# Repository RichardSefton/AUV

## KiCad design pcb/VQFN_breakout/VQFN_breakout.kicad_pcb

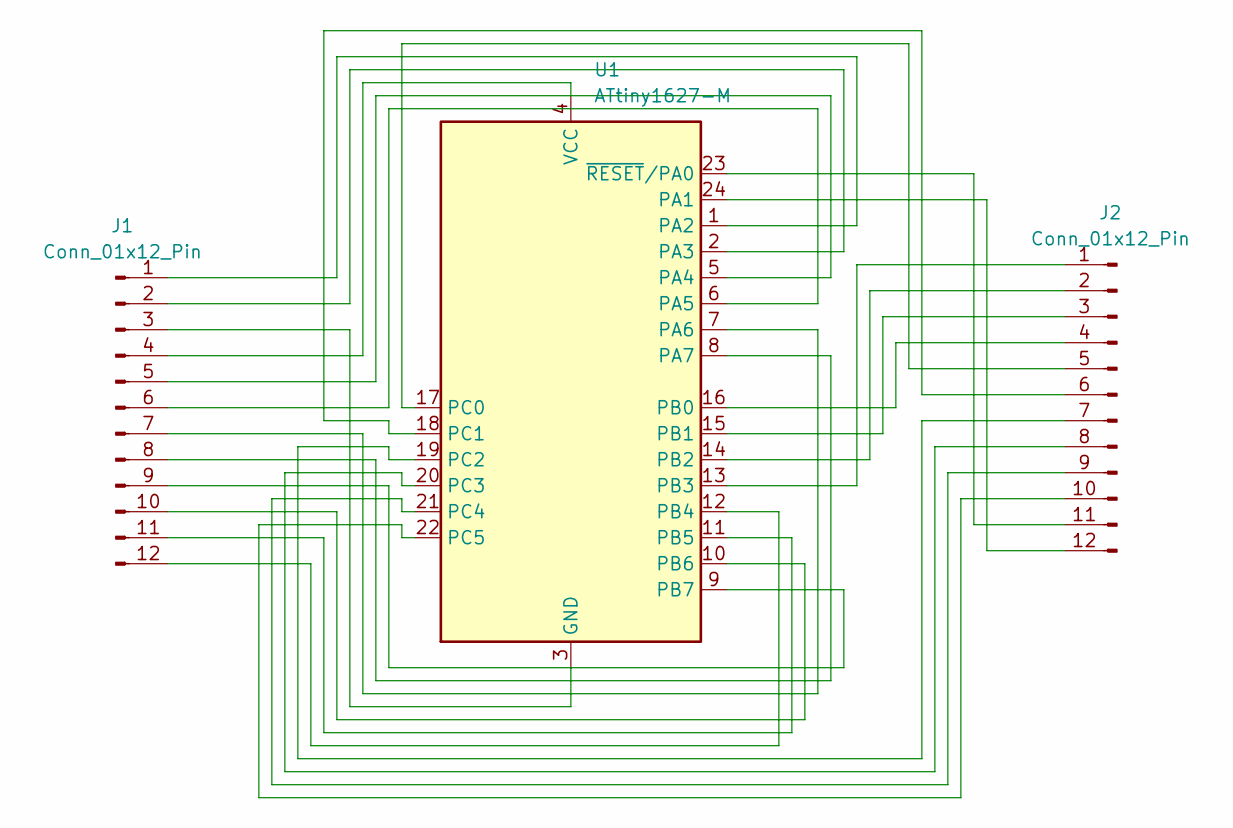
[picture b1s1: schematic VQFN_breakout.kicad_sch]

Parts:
J1, J2: Conn_01x12_Pin; PinSocket_1x12_P2.54mm_Vertical
U1: ATtiny1627-M; QFN-24-1EP_4x4mm_P0.5mm_EP2.6x2.6mm

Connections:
unnamed: J1.1, U1.1 (PA2)
unnamed: J1.2, U1.2 (PA3)
unnamed: J1.3, U1.3 (GND), U1.25 (GND)
unnamed: J1.4, U1.4 (VCC)
unnamed: J1.5, U1.5 (PA4)
unnamed: J1.6, U1.6 (PA5)
unnamed: J1.7, U1.7 (PA6)
unnamed: J1.8, U1.8 (PA7)
unnamed: J1.9, U1.9 (PB7)
unnamed: J1.10, U1.10 (PB6)
unnamed: J1.11, U1.11 (PB5)
unnamed: J1.12, U1.12 (PB4)
unnamed: J2.1, U1.13 (PB3)
unnamed: J2.2, U1.14 (PB2)
unnamed: J2.3, U1.15 (PB1)
unnamed: J2.4, U1.16 (PB0)
unnamed: J2.5, U1.17 (PC0)
unnamed: J2.6, U1.18 (PC1)
unnamed: J2.7, U1.19 (PC2)
unnamed: J2.8, U1.20 (PC3)
unnamed: J2.9, U1.21 (PC4)
unnamed: J2.10, U1.22 (PC5)
unnamed: J2.11, U1.23 (~RESET/PA0)
unnamed: J2.12, U1.24 (PA1)

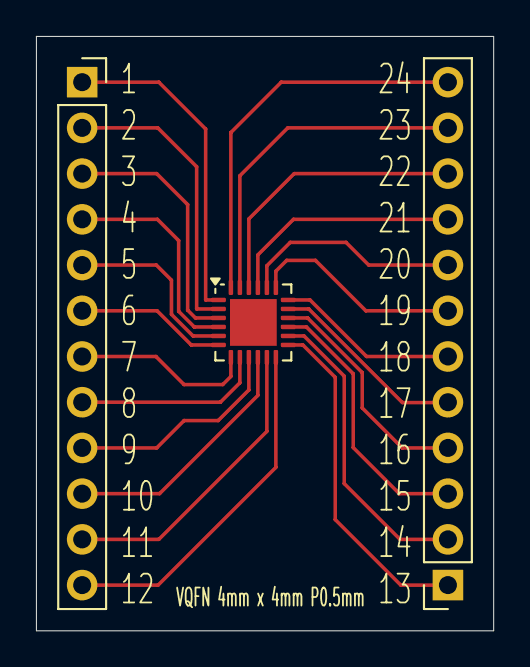
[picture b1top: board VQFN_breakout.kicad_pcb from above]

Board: 2 copper layers, 25.4 x 33.0 mm, 3 parts (0 on the bottom side), 24 nets.

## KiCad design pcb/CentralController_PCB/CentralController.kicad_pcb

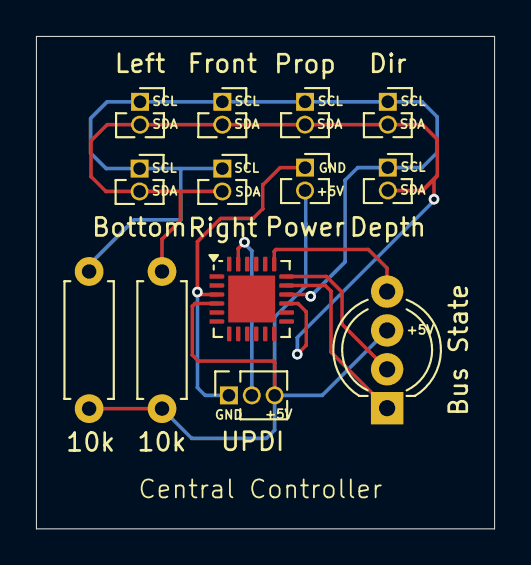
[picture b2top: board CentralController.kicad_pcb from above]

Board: 2 copper layers, 25.5 x 27.4 mm, 13 parts (0 on the bottom side), 8 nets.

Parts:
D1: Bus State; LED_D5.0mm-4_RGB_Wide_Pins
J1: Front; PinSocket_1x02_P1.27mm_Vertical
J2: Left; PinSocket_1x02_P1.27mm_Vertical
J3: Right; PinSocket_1x02_P1.27mm_Vertical
J4: Bottom; PinSocket_1x02_P1.27mm_Vertical
J5: Power; PinSocket_1x02_P1.27mm_Vertical
J5#2: Prop; PinSocket_1x02_P1.27mm_Vertical
J6: Dir; PinSocket_1x02_P1.27mm_Vertical
J7: Depth; PinSocket_1x02_P1.27mm_Vertical
J8: UPDI; PinSocket_1x03_P1.27mm_Vertical
R1, R2: 10k; R_Axial_DIN0207_L6.3mm_D2.5mm_P7.62mm_Horizontal
U1: ATtiny1627; QFN-24-1EP_4x4mm_P0.5mm_EP2.6x2.6mm

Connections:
+5V: D1.3 (GK), J5.2, J8.3, R1.2, R2.2, U1.4 (VCC)
GND: J5.1, J8.1, U1.3 (GND)
unnamed: D1.1 (A), U1.17 (PC0)
unnamed: D1.2 (RK), U1.18 (PC1)
unnamed: D1.4 (BK), U1.19 (PC2)
unnamed: J1.1, J2.1, J3.1, J4.1, J5#2.1, J6.1, J7.1, R1.1, U1.16 (PB0)
unnamed: J1.2, J2.2, J3.2, J4.2, J5#2.2, J6.2, J7.2, R2.1, U1.15 (PB1)
unnamed: J8.2, U1.23 (~RESET/PA0)

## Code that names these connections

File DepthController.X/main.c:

/**
 * This is the depth controller for the submarine. 
 * 
 * This is a stepper motor connected to a convertor of my own design to convert
 * linear to rotary force. Its basically a screw connected to a large nut with a housing for the syringe 
 * plunger. 
 * 
 * So basically this controller needs to control the stepper motor in two directions (forward
 * and reverse), and also make sure the motor does not turn beyond a certain point in either direction. 
 * 
 * Basically we need a way to track the position of the nut. 
 */

//Lets get the basics out the way. 
#define F_CPU 3333333UL
#include <avr/io.h>
#include <avr/delay.h>
#include <avr/interrupt.h>

void MainClkCtrl(void);

/**
 * Need a way to track the position. I'm thinking an array. As the motor turns, 
 * every second or so we can either increment or decrement the array based on direction. 
 * 
 * If the array is at the start of end, we can't progress. It would be neat. As long 
 * as theres no reset of the device. 
 * 
 * Option 2 would be a wire and a contact plate so we know where at the start or the
 * end of the rail.
 * 
 * I think both. So in cases where the device has no power at non-start or stop position its 
 * reference isn't completely lost. 
 * 
 * To traverse the array we'll have a Timer Counter that will increment the index after a 
 * set period
 */
volatile int pos[1024];
void PosSetup(void);
void BufferSetup(void);
void RTCSetup(void);
void PosDec(void);
void PosInc(void);

/*
 * Motor driver. We can steal this from the midterm prototype. which in itself was 
 * stolen from some forum describing how to use stepper motors with arduino. I think it 
 * was the original stepper motor datasheet but this was a while ago. - I just read its
 * comments. It was from the datasheet
 * 
 * So we need a digital write function
 * 
 * We also need to rejig the pins its using. 
 * 
 * And have a setup function to setup the pins 
 */
void MotorSetup(void);
void StepperMotorStep(uint8_t);
void digitalWrite(uint8_t, uint8_t);
#define HIGH 0x01
#define LOW 0x00
//Contols the step
volatile int8_t step = 0x00; //needs to be signed so it can slip into negative values

/**
 * Need a way to control the direction. We'll use some constants and a direction variable
 * 
 * There are 3 possible directions. UP, DOWN and NONE
 */
#define UP 0
#define NONE 1
#define DOWN 2
volatile uint8_t dir = 1;

int main(void)
{
    MainClkCtrl();
    PosSetup(); 
    BufferSetup();
    
    while(1)
    {
        //1 is the marker number. If the element is 1, it means the device thinks the 
        //nut is in that position. so we won't go any further. 
        if (dir == UP && pos[1023] != 1)
        {
            stepperMotorStep(step);
            step--;
        }
        else if (dir == DOWN && pos[0] != 1)
        {
            stepperMotorStep(step);
            step++;
        }
        
        //Keep the step in bounds
        if(step > 0x07)
        {
            step = 0x00;
        }

        if(step < 0x00)
        {
            step = 0x07;
        }
        
        _delay_us(750); //controls the speed. Adjust as needed. 
    }
    
    return 0;
}

/**
 * I think I've mentioned this in a previous part. This MCU has a default clock speed
 * of 3.33MHz. (20MHz with a default prescaler of 6). These settings are fine so we're 
 * just going to make it explicit. 
 */
void MainClkCtrl(void) 
{
    _PROTECTED_WRITE(CLKCTRL.MCLKCTRLA, CLKCTRL_CLKSEL_OSC20M_gc | CLKCTRL_CLKOUT_bm);
    _PROTECTED_WRITE(CLKCTRL.MCLKCTRLB, CLKCTRL_PDIV_6X_gc | CLKCTRL_PEN_bm);
}

/*
 * Basically we're going to 0 the array and make the midpoint (512) 1. 
 * It will sort itself out in travel with the buffer
 */
void PosSetup(void)
{
    for (int i = 0; i < 1024; i++)
    {
        pos[i] = 0;
    }
    pos[512] = 1;
}

/**
 Buffer setup is the setup function for the start/stop plate we can use to reset the array to
 * make sure we don't go out of bounds.
 */
void BufferSetup(void)
{
    //Pins to avoid are 15(PB1) and 16(PB0) as these are SDA and SCL respectively. 
    //also 23 (PA0) is the UPDI pin. 
    
    //Going to use 6(PA5), 7(PA6). These need to be inputs to detect voltage
    PORTA.DIR &= ~(PIN5_bm | PIN6_bm);
    
    //Gonna need the interrupts on these
    PORTA.PIN5CTRL |= PORT_ISC_RISING_gc;
    PORTA.PIN6CTRL |= PORT_ISC_RISING_gc;
}

/**
 * Setup the RTC to count periods of time to control the motor position
 */
void RTCSetup(void)
{
    
}

/**
 * Pos mover. 
 */
void PosDec(void)
{
    int index = 0;
    for (int i = 0; i < 1024; i++)
    {
        if (pos[i] == 1)
        {
            index = i;
        }
        pos[i] = 0;
    }
    pos[index - 1] = 1;
}
void PosInc(void)
{
    int index = 0;
    for (int i = 0; i < 1024; i++)
    {
        if (pos[i] == 1)
        {
            index = i;
        }
        pos[i] = 0;
    }
    pos[index + 1] = 1;
}

/**
 * Need to setup the pins for the stepper motor. Because of the digital write function 
 * we need to keep them on the same port. 
 * 
 * We'll use port c. 
 * 17 - PC0
 * 18 - PC1
 * 19 - PC2
 * 20 - PC3
 */
void MotorSetup(void)
{
    PORTC.DIR |= PIN0_bm | PIN1_bm | PIN2_bm | PIN3_bm;
}

/*
 * This function will drive the stepper motor. The sequance depends on the step
 */
void stepperMotorStep(int8_t step)
{
    //This is basically from the datasheet http://eeshop.unl.edu/pdf/Stepper+Driver.pdf
    //Made the digitalWrite function to keep it inline. 
    switch (step)
    {
        case 0:
            digitalWrite(PIN0_bm, LOW);
            digitalWrite(PIN1_bm, LOW);
            digitalWrite(PIN2_bm, LOW);
            digitalWrite(PIN3_bm, HIGH);
            break;
        case 1:
            digitalWrite(PIN0_bm, LOW);
            digitalWrite(PIN1_bm, LOW);
            digitalWrite(PIN2_bm, HIGH);
            digitalWrite(PIN3_bm, HIGH);
            break;
        case 2:
            digitalWrite(PIN0_bm, LOW);
            digitalWrite(PIN1_bm, LOW);
            digitalWrite(PIN2_bm, HIGH);
            digitalWrite(PIN3_bm, LOW);
            break;
        case 3:
            digitalWrite(PIN0_bm, LOW);
            digitalWrite(PIN1_bm, HIGH);
            digitalWrite(PIN2_bm, HIGH);
            digitalWrite(PIN3_bm, LOW);
            break;
        case 4:
            digitalWrite(PIN0_bm, LOW);
            digitalWrite(PIN1_bm, HIGH);
            digitalWrite(PIN2_bm, LOW);
            digitalWrite(PIN3_bm, LOW);
            break;
        case 5:
            digitalWrite(PIN0_bm, HIGH);
            digitalWrite(PIN1_bm, HIGH);
            digitalWrite(PIN2_bm, LOW);
            digitalWrite(PIN3_bm, LOW);
            break;
        case 6:
            digitalWrite(PIN0_bm, HIGH);
            digitalWrite(PIN1_bm, LOW);
            digitalWrite(PIN2_bm, LOW);
            digitalWrite(PIN3_bm, LOW);
            break;
        case 7:
            digitalWrite(PIN0_bm, HIGH);
            digitalWrite(PIN1_bm, LOW);
            digitalWrite(PIN2_bm, LOW);
            digitalWrite(PIN3_bm, HIGH);
            break;
    }
}
void digitalWrite(uint8_t pin, uint8_t value)
{
    if (value == LOW)
    {
        PORTC.OUTCLR = pin;
    }
    else
    {
        PORTC.OUTSET = pin;
    }
}

ISR(PORTA_PORT_vect)
{
    //Two pins that could trigger this. Need to handle each one differently
    //5 We'll have as the near end
    if (PORTA.INTFLAGS & PIN5_bm) {
        //I know normally we would use the size of the array but in c we need to calculate this. 
        //Its sizeof the array / sizeof the first element. We know the size and its not going to change. 
        //so we'll just use that..
        for (int i = 0; i < 1024; i++)
        {
            pos[i] = 0;
        }
        pos[1023] = 1;
        
        //Clear the flag so it can be raised in the future
        PORTA.INTFLAGS = PIN5_bm;
    }

    if (PORTA.INTFLAGS & PIN6_bm) {
        for (int i = 0; i < 1024; i++)
        {
            pos[i] = 0;
        }
        pos[0] = 1;
        
        //Clear the flag so it can be raised in the future
        PORTA.INTFLAGS = PIN6_bm;
    }
}

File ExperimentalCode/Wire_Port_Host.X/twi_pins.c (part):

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  // On parts where this erratum has been fixed, we shouldn't need to do *anything* for this!
  #if defined(PORTMUX_TWIROUTEA) // AVR Dx or Ex-series
    // Mux options for Dx/Ex-series TWI 0:
    // PA2, PA3, PC2, PC3 - Default
    // PA2, PA3, PC6, PC7 - Alt 1
    // PC2, PC3, PC6, PC7 - Alt 2
    // PA0, PA1, PC2, PC3 - Alt 3, not available on DA, DB
    #if defined(__AVR_DA__) || defined(__AVR_DB__)
      uint8_t portmux = PORTMUX.TWIROUTEA & PORTMUX_TWI0_gm; // registers are volatile, so it's bulky to recheck multiple times.
      if (portmux == PORTMUX_TWI0_ALT2_gc) {
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    #endif
  #elif defined(PORTMUX_TWISPIROUTEA)
    // Mux options for megaAVR 0-series:
    // PA2, PA3, PC2, PC3 - Default
    // PA2, PA3, PF2, PF3 - Alt 1
    // PC2, PC3, PF2, PF3 - Alt 2
    uint8_t portmux = PORTMUX.TWISPIROUTEA & PORTMUX_TWI0_gm; // registers are volatile, so it's bulky to recheck multiple times.
    if (portmux == PORTMUX_TWI0_ALT2_gc) {
      PORTC.OUTCLR = 0x0C;  // bits 2 and 3
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        if ((PORTMUX.CTRLB & PORTMUX_TWI0_bm)) {
          // make sure we don't get errata'ed - make sure their bits in the
          // PORTx.OUT registers are 0.
          PORTA.OUTCLR = 0x06;  // if swapped it's on PA1, PA2
        } else {
          PORTB.OUTCLR = 0x03;  // else PB0, PB1
        }
      #elif defined(__AVR_ATtinyxy2__)
        PORTA.OUTCLR = 0x06;  // 8-pin parts always have it on PA1/2
      #else
        PORTB.OUTCLR = 0x03;  // else it's 0-series or 2-series. Either way, there's no remapping: it's on PB0, PB1
      #endif
    #endif
  #else
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        } else {
          // Assume default configuration
          #if defined(__AVR_DD__)   /* DD with 14 pins has no default pins in the "default" "position! Default to alt=2 */
            PORTMUX.TWIROUTEA = portmux | PORTMUX_TWI0_ALT2_gc;  // Alt2 pins:  PC2, PC3, PC6, PC7
          #else
            PORTMUX.TWIROUTEA = portmux;
          #endif
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  #elif defined(PORTMUX_TWIROUTEA) /* AVR Dx-series */
    uint8_t portmux = PORTMUX.TWIROUTEA & (~PORTMUX_TWI0_gm);
    #if defined(PIN_WIRE_SDA_PINSWAP_3)
      if (state == 3) { /* PA0, PA1, PC2, PC3 */
        // Use pin swap
        PORTMUX.TWIROUTEA = portmux | PORTMUX_TWI0_ALT3_gc;
        return true;
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        PORTMUX.TWIROUTEA = portmux;
        return state == 0;
      }
    #else // DD with no PA2/3 so "default" is alt2
      {
        PORTMUX.TWIROUTEA = portmux | PORTMUX_TWI0_ALT2_gc;
        return false; // on a DD14, hence without PA2, PA3, Wire.swap(0) and Wire.swap(1) are invalid, Wire.swap(2) and Wire.swap(3) are valid - but we tested for those already. Hence, if we're here,
      }
    #endif
  #elif defined(PORTMUX_TWISPIROUTEA) // megaAVR 0-series
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      } else {
        return (VPORTB.IN & 0x03);
      }
    #elif defined(__AVR_ATtinyxy2__)  // No PORTMUX for 8-pin parts, they always use PA1/2
      return ((VPORTA.IN & 0x06) >> 1);
    #else //it uses PB0/1
      return (VPORTB.IN & 0x03);
    #endif
  #else
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
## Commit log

2024-05-29 Initial code dump.
    This commit includes the initial proof of concepts for I2C protocol between an host and client (working state) and also the
    currently ongoing sonar proof of concept which is currently transmitting on 40kHz to a 40kHz transducer.
2024-05-29 Added the PCB Breakout design for VQFN packaged chips. This includes the gerber files used by the company who fabricated the boards.
2024-05-29 Added the i2c proof of concept kicad drawings (circuit diagram)
2024-06-08 Sonar in a working state with the current circuit diagram for it. (in the kicad drawings)
2024-06-09 Added i2c controller for sonar.
    This is working, but the sonar module itself is still being troublesome.
    It is not giving an accurate time. not sure why.
2024-06-09 Push before a rework
    I want to swap out TCB1 for RTC for greater accuracy.
2024-06-12 Added stepper motor driver test script ready for the prototype. Just needs i2c integration at this point.
    And some logic to control what it does when it receives a command. Maybe a command list or something?
2024-06-12 Added Prototype (for midterm) module projects.
    Projects added are a prototype motor controller, HC-SR04 based sonar module, and a controller
    All modules are i2c connected with the controller set as the host.
    In its current state its time to expand the I2C libraries to accomodate read operations.
2024-06-13 Read operations appears to be working but no way to verify fully
    Distance is not 100% accurate yet
2024-06-13 I2C Read oiperation is sending correct data.
    Current issue to resolve is the I2C rail doesn't handle multiple devices correctly.
    I think this is to do with arbitration rules.
2024-06-14 I2C Broken but maybe salvageable?
2024-06-14 Refactored the I2C/TWI library.
    This should be a more stable version now. Developed inline with the datasheet.
    Still has a lot of work to be viable for wider applications, but at least for
    this prototype it should hold up. It just has to work for a weekend.
2024-06-15 Added LED Debug functions and colour defs
2024-06-15 Took hours and hours but a working prototype has been acheived!
2024-07-02 Made more models. Waiting to see if current ones fit once fabricated.
2024-07-21 Big push. Lots of things. Can't remember what.
2024-07-31 Been a while. Multiple changes and iterations.
2024-08-01 Made start on central controller.
2024-08-06 About to make changes to TWI library.
2024-08-07 The Depth Controller and Central Controller are talking to one another.
    Need to reintegrate the sonar module to get the 3 modules working in tandem.
2024-08-09 central controller doesnt seem to want to work with peripherals enabled.
2024-08-12 Communication (TWI) is not quite working. Central controller seems to be at fault
    Or at least I think it is. The device seems to reset and other peripherals
    (RTC) do not have working ISRs so thats why the assumption is this is the fault.
2024-08-12 Still not working but exploring other avenues as a fallback
2024-08-15 Still not working. trying to port Wire.h
2024-08-15 CWire added
    Still not working but I think its the best hope.
    Its a hacked version of Wire for arduino from megaTinyCore. Rewritten in C and hopefully
    decoupled.
2024-08-16 Appears to be working for write operations. Need to expand and test
    Also just as a note it seems connected i2c devices need a common power source.
2024-08-16 Converted CWire to a library project.
2024-08-16 Working on read and write operations.
    This is a hacked version or Wire from megaTinyCore. converted to C and dependencies removed.
    megatinycore version is used because it contains the correct registers.
2024-08-19 i2c working and adding more modules.
    converted the common code to library projects.
2024-08-20 Interconnected devices working. Need 2 more sonar and directional motor
2024-08-20 Added the other 2 sonar modules.
2024-09-02 final version of the code
2024-09-02 report started
2024-09-02 Added midterm report so I can work on it elsewhere
2024-09-03 Updated Final Report.
    Added some assets to the report for importing to appendices.
2024-09-03 First draft of Design portion of the FinalReport
2024-09-04 Added implementation section to report
2024-09-05 Added testing section
2024-09-07 Final push

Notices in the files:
ExperimentalCode/Wire_Port_Host.X/twi_pins.c:
Copyright (c) 2006 Nicholas Zambetti.  All right reserved.
